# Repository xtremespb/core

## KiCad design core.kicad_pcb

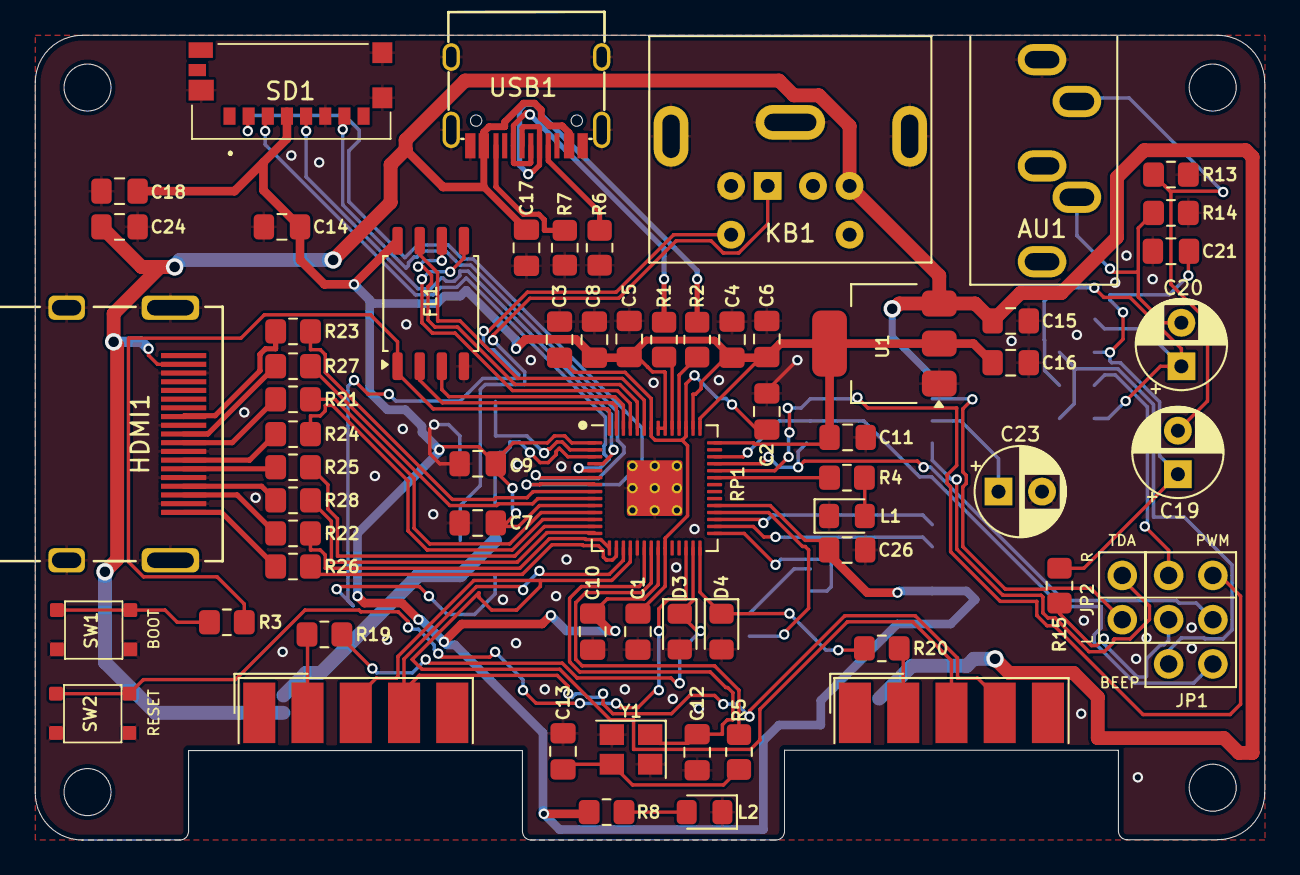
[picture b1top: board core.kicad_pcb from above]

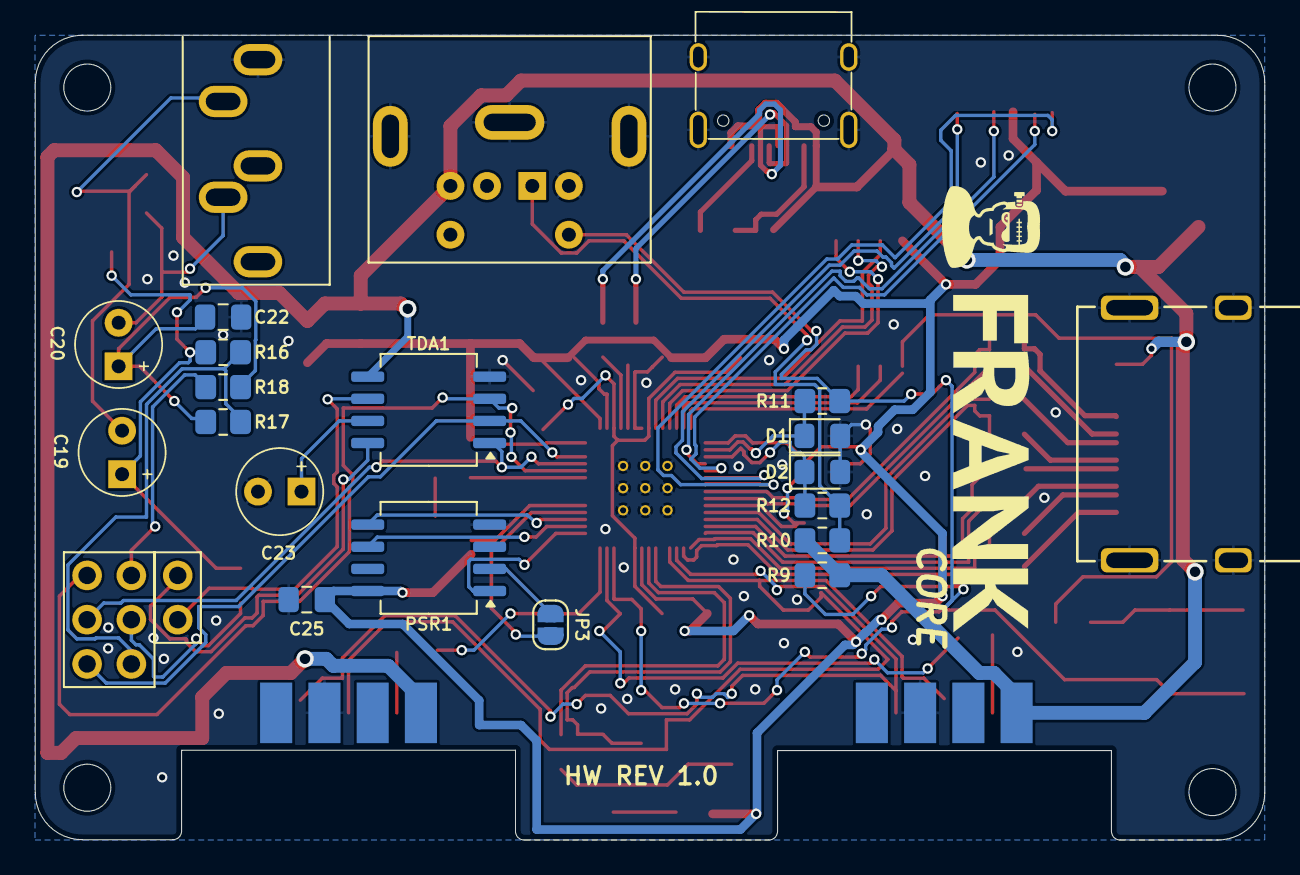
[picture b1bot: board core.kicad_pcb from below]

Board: 2 copper layers, 70.6 x 46.2 mm, 82 parts (14 on the bottom side), 72 nets.

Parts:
AU1: AUDIO OUT; Medved_Jack_3.5mm_CUI_SJ1-3535NG_Horizontal
C1, C2, C4, C6, C7, C8, C9, C10, C11, C14, C26: 100n; Medved_C_0805
C3, C5: 1u; Medved_C_0805
C12, C13: 15p; Medved_C_0805
C15, C16: 10u; Medved_C_0805
C17, C18, C24, C25: 0.1u; Medved_C_0805
C19, C20, C23: 10u; Medved_CP_Radial_D5.0mm_P2.50mm
C21, C22: 10n; Medved_C_0805
D1, D2, D3, D4: 3V3; Medved_D_0805
FL1: W25Q128JVS; Medved_SOIC-8_5.23x5.23mm_P1.27mm
H1, H2, H3, H4: MountingHole; MountingHole_2.7mm
HDMI1: HDMI
JOY1, JOY2: Joystick; DSUB-9
JP1: Audio Jumpers; Medved_JMP_2x03
JP2: I2S; Medved_PinHeader_1x02
JP3: JMP PSRAM; Medved_Jumper_Solder
KB1: PS/2; Connector_Mini-DIN_Female_6Pin_2rows
L1: LED; Medved_L_0805
L2: GREEN; Medved_L_0805
PSR1: PSRAM; SO-8_5.3x6.2mm_P1.27mm
R1, R2: 27; Medved_R_0805
R3, R5, R9, R10, R15, R18, R19, R20: 1k; Medved_R_0805
R4, R8: 1K; Medved_R_0805
R6, R7: 5.1K; Medved_R_0805
R11, R12: 100R; Medved_R_0805
R13, R14: 330R; Medved_R_0805
R16, R17: 2k; Medved_R_0805
R21, R22, R23, R24, R25, R26, R27, R28: 270R; Medved_R_0805
RP1: RP2040; RP2040-QFN-56
SD1: 47571-0001; microsd
SW1: Flash Button; Button_SMD_3x3x2
SW2: Reset Button; Button_SMD_3x3x2
TDA1: TDA1387T; SO-8_5.3x6.2mm_P1.27mm
U1: NCP1117-3.3_SOT223; Medved_SOT-223-3_TabPin2
USB1: USB Type C; USB-TYPE-C-31-M-12_lib2
Y1: 12 MHz; Medved_CRYSTAL_3225

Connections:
+3V3: C4.1, C5.1, C6.1, C7.1, C8.1, C9.1, C10.1, C11.1, C14.1, C16.1, C18.2, C25.1, C26.1, FL1.8 (VCC), PSR1.8 (VCC), R8.2, RP1.1 (IOVDD), RP1.10 (IOVDD), RP1.22 (IOVDD), RP1.33 (IOVDD), RP1.42 (IOVDD), RP1.43 (ADC_AVDD), RP1.44 (VREG_IN), RP1.48 (USB_VDD), RP1.49 (IOVDD), SD1.P4 (VDD), U1.2 (VO)
/AU_DATA: JP1.2, RP1.38 (GPIO26_ADC0), TDA1.3 (DATA)
/AU_LRCK: JP1.6, RP1.40 (GPIO28_ADC2), TDA1.2 (LRCK)
/AU_SCLK: JP1.4, RP1.39 (GPIO27_ADC1), TDA1.1 (SCLK)
/Audio/BEEP_OUT: JP1.5, R16.2, R17.2
/Audio/FLT: C23.1, TDA1.7 (FLT)
/Audio/L: AU1.T, C19.2, R13.1
/Audio/LEFT_OUT: JP1.3, R15.2
/Audio/LEFT_TDA: JP2.2, TDA1.6 (A_LEFT)
/Audio/R: AU1.R, C20.2, R14.1
/Audio/RIGHT_OUT: JP1.1, R18.2
/Audio/RIGHT_TDA: JP2.1, TDA1.8 (A_RIGHT)
/D+: R1.1, USB1.6 (DP1), USB1.8 (DP2)
/D-: R2.1, USB1.5 (DN2), USB1.7 (DN1)
/GP1_DATA: D3.1 (K), R19.1, RP1.27 (GPIO16)
/GP2_DATA: D4.1 (K), R20.1, RP1.28 (GPIO17)
/GP_J3: JOY1.3, JOY2.3, RP1.18 (GPIO15)
/GP_J4: JOY1.4, JOY2.4, RP1.17 (GPIO14)
/HDMI_CLKN: R23.2, RP1.8 (GPIO6)
/HDMI_CLKP: R27.2, RP1.9 (GPIO7)
/HDMI_D0N: R21.2, RP1.11 (GPIO8)
/HDMI_D0P: R24.2, RP1.12 (GPIO9)
/HDMI_D1N: R25.2, RP1.13 (GPIO10)
/HDMI_D1P: R28.2, RP1.14 (GPIO11)
/HDMI_D2N: R22.2, RP1.15 (GPIO12)
/HDMI_D2P: R26.2, RP1.16 (GPIO13)
/PS2_CLK: D1.1 (K), R11.2, RP1.2 (GPIO0)
/PS2_DATA: D2.1 (K), R12.2, RP1.3 (GPIO1)
/PSR_CE: PSR1.1 (~CE), RP1.29 (GPIO18)
/PSR_SCLK: PSR1.6 (SCLK), RP1.30 (GPIO19)
/PSR_SISIO: PSR1.5 (SI/SIO), RP1.31 (GPIO20)
/PSR_SOSIO: JP3.2 (B), RP1.32 (GPIO21)
/RP2040/GPIO25: R4.2, RP1.37 (GPIO25)
/RP2040/QSPI_SCLK: FL1.6 (CLK), RP1.52 (QSPI_SCLK)
/RP2040/QSPI_SD0: FL1.5 (DI(IO0)), RP1.53 (QSPI_SD0)
/RP2040/QSPI_SD1: FL1.2 (DO(IO1)), RP1.55 (QSPI_SD1)
/RP2040/QSPI_SD2: FL1.3 (IO2), RP1.54 (QSPI_SD2)
/RP2040/QSPI_SD3: FL1.7 (IO3), RP1.51 (QSPI_SD3)
/RP2040/QSPI_SS: FL1.1 (~CS), R3.1, RP1.56 (QSPI_SS)
/RP2040/XIN: C12.1, RP1.20 (XIN), Y1.1
/RP2040/XOUT: R5.1, RP1.21 (XOUT)
/RP2040/~USB_BOOT: R3.2, SW1.3, SW1.4
/RUN: RP1.26 (RUN), SW2.3, SW2.4
/SD_CLK: RP1.4 (GPIO2), SD1.P5 (CLK)
/SD_CMD: RP1.5 (GPIO3), SD1.P3 (CMD)
/SD_DAT0: RP1.6 (GPIO4), SD1.P7 (DAT0)
/SD_DAT3: RP1.7 (GPIO5), SD1.P2 (CD/DAT3)
GND: AU1.S, C1.2, C2.2, C3.2, C4.2, C5.2, C6.2, C7.2, C8.2, C9.2, C10.2, C11.2, C12.2, C13.2, C14.2, C15.2, C16.2, C17.2, C18.1, C21.2, C22.2, C23.2, C24.2, C25.2, C26.2, D1.2 (A), D2.2 (A), D3.2 (A), D4.2 (A), FL1.4 (GND), HDMI1.2 (G_D2), HDMI1.5 (G_D1), HDMI1.8 (G_D0), HDMI1.11 (G_CLK), HDMI1.17 (G_DDC/CEC), HDMI1.20 (SHIELD1), HDMI1.21 (SHIELD2), HDMI1.22 (SHIELD3), HDMI1.23 (SHIELD4), JOY1.8, JOY2.8, KB1.3, L1.1 (K), L2.1 (K), PSR1.4 (VSS), R6.1, R7.1, R13.2, R14.2, RP1.19 (TESTEN), RP1.57 (GND), SD1.G1 (GND_1), SD1.G2 (GND_2), SD1.G3 (GND_3), SD1.P6 (VSS), SW1.1, SW1.2, SW2.1, SW2.2, TDA1.4 (AGND), U1.1 (GND), USB1.1 (GND), USB1.12 (GND), USB1.13 (SHIELD), Y1.2, Y1.4
unnamed: C13.1, R5.2, Y1.3
unnamed: C19.1, C21.1, R15.1, R16.1
unnamed: C20.1, C22.1, R17.1, R18.1
unnamed: HDMI1.12 (CLKN), R23.1
unnamed: HDMI1.10 (CLKP), R27.1
unnamed: HDMI1.9 (D0N), R21.1
unnamed: HDMI1.7 (D0P), R24.1
unnamed: HDMI1.6 (D1N), R25.1
unnamed: HDMI1.4 (D1P), R28.1
unnamed: HDMI1.3 (D2N), R22.1
unnamed: HDMI1.1 (D2P), R26.1
unnamed: JOY1.2, R19.2
unnamed: JOY2.2, R20.2
unnamed: JP3.1 (A), PSR1.2 (SO/SIO)
unnamed: KB1.1, R10.2, R12.1
unnamed: KB1.5, R9.2, R11.1
unnamed: L1.2 (A), R4.1
unnamed: L2.2 (A), R8.1
unnamed: R2.2, RP1.46 (USB_DM)
unnamed: R1.2, RP1.47 (USB_DP)
unnamed: C1.1, C2.1, C3.1, RP1.23 (DVDD), RP1.45 (VREG_VOUT), RP1.50 (DVDD)
unnamed: R6.2, USB1.4 (CC1)
unnamed: R7.2, USB1.10 (CC2)
VBUS: C15.1, C17.1, C24.1, HDMI1.18 (+5V), JOY1.6, JOY2.6, KB1.4, R9.1, R10.1, TDA1.5 (VA), U1.3 (VI), USB1.2 (VBUS), USB1.11 (VBUS)

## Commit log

2024-12-17 HW Rev 1.0
2024-12-17 Gerbers added
